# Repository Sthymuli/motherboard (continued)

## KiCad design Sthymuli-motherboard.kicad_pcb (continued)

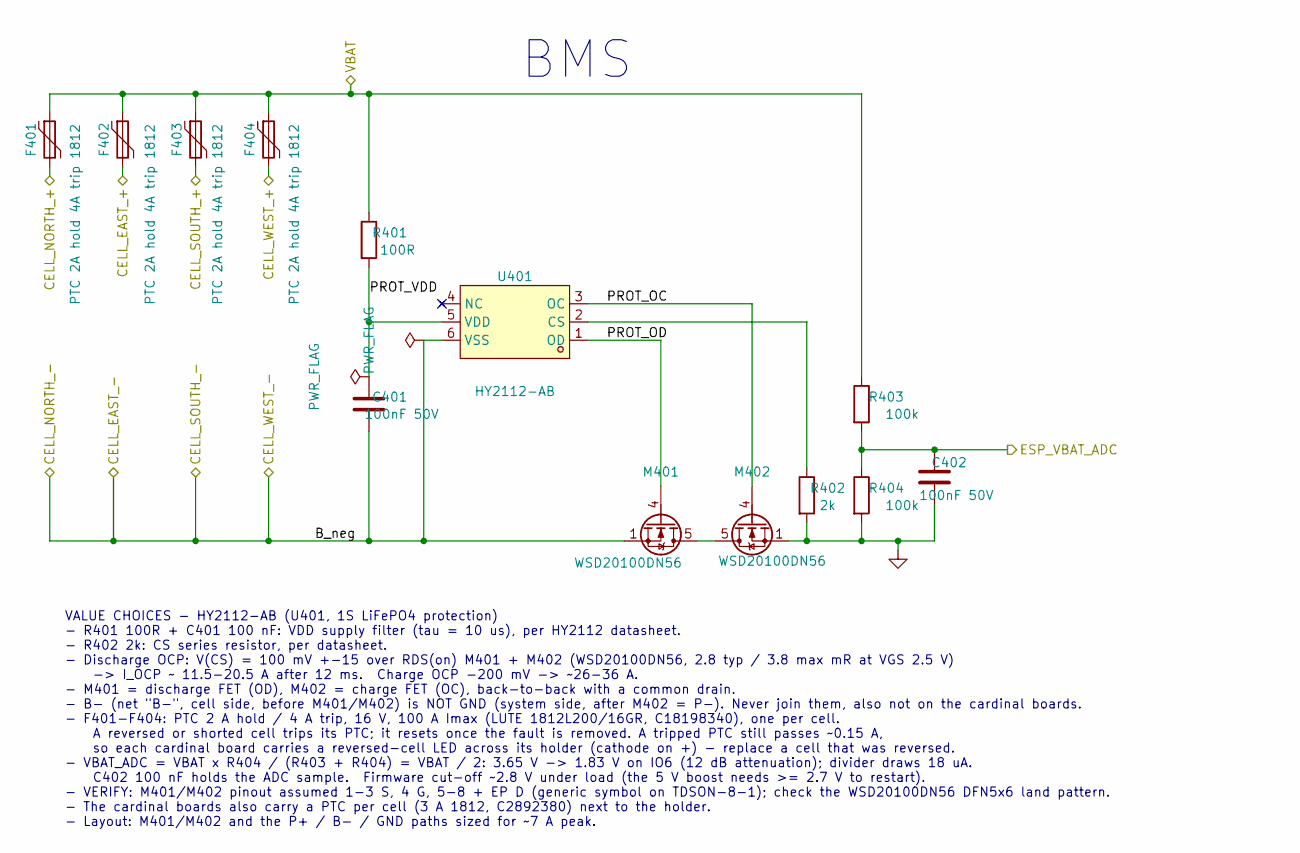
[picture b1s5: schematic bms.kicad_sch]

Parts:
C401, C402: 100nF 50V; C_0603_1608Metric; LCSC C14663
F401, F402, F403, F404: PTC 2A hold 4A trip 1812; F1812; MPN BSMD2920-400-24V; LCSC C18198340
M401, M402: WSD20100DN56; TDSON-8-1; LCSC C5185318
R401: 100R; R_0603_1608Metric; LCSC C22775
R402: 2k; R_0603_1608Metric; LCSC C22975
R403, R404: 100k; R_0603_1608Metric; LCSC C25803
U401: HY2112-AB; SOT-23-6_L2.9-W1.6-P0.95-LS2.8-BR; LCSC C168763

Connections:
/BMS/PROT_OC: M402.4 (G), U401.3 (OC)
/BMS/PROT_OD: M401.4 (G), U401.1 (OD)
/BMS/PROT_VDD: C401.1, R401.2, U401.5 (VDD)
/BMS/VBAT: F401.1, F402.1, F403.1, F404.1, R401.1, R403.1; also elsewhere on the board
B-: C401.2, M401.1 (S), M401.2 (S), M401.3 (S), U401.6 (VSS); also elsewhere on the board
BAT+EAST: F402.2; also elsewhere on the board
BAT+NORTH: F401.2; also elsewhere on the board
BAT+SOUTH: F403.2; also elsewhere on the board
BAT+WEST: F404.2; also elsewhere on the board
ESP_VBAT_ADC: C402.1, R403.2, R404.1; also elsewhere on the board
GND: C402.2, M402.1 (S), M402.2 (S), M402.3 (S), R402.2, R404.2; also elsewhere on the board
unnamed: M401.5 (D), M402.5 (D)
unnamed: R402.1, U401.2 (CS)

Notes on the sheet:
BMS
VALUE CHOICES - HY2112-AB (U401, 1S LiFePO4 protection) - R401 100R + C401 100 nF: VDD supply filter (tau = 10 us), per HY2112 datasheet. - R402 2k: CS series resistor, per datasheet. - Discharge OCP: V(CS) = 100 mV +-15 over RDS(on) M401 + M402 (WSD20100DN56, 2.8 typ / 3.8 max mR at VGS 2.5 V) -> 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

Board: 4 copper layers, 183 parts (83 on the bottom side), 144 nets, no tracks yet.

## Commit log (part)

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2026-04-27 Update link format for cardinal board in README
